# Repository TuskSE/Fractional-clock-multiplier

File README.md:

# Fractional Clock Multiplier (wip)
8hp algorithmic rhythm-generation module for Eurorack, powered by the Teensy LC

Currently two main modes:
* Fractional Multiplication and division of steady or slowly-varying clock inputs.
  * No requirement for clock input to be multiple ppqn, as the clock input is predictive. I'd like to update this so it can deal with swung input also
* Generation of euclidean rhythms ( see [Toussaint 2005](http://cgm.cs.mcgill.ca/~godfried/publications/banff.pdf) ) from arbitrary (regular or non-regular) clock input 

Output can be shifted either by beat-quantized or subquantized amounts, and optionally recombined with the input. This can be used to generate swung clock output for example, or controlled via CV to generate complex compound rhythms. 

Selectable trigger/gate output modes. 

Assignable CV control over all paramaters, with attenuverter. 

Current schematic, panel mockup and PCB design:

An older prototype:

<img src="https://lh3.googleusercontent.com/F2FJkoGD_2Y6mUCA_72Tr9jKIQL8T51u-yPpXMLdA85AF7AUzsiI0R6vGA8PAkv26-s6BQ4YR2C6YWq7D_WIugwAtMuLFM5RAIA3TbphAoilKe7S2X2kTRAt2BslmQAuLZtmlxdI60x7pljAAfFQjpe4ux4xAhEyvlYldTjiMu7CKEfx0s5RLvJsloXXFzuWYh74JVn_ynYBdR5kknDmDOABy-btkMf6ygelY21k-5Sk13OeYi_4nqbalsbw_Kay20YbHjPqkHRQ4EJwRg-HghsKRhGDjyb66y0XgOmLnHMniq8GFPWXzc7Ou17aOJmmEo-iptwhYquIdqMTw5126-4uQ4JN-fbZk5uMNa9TVr03RODQvABWOTEXRQ_gDacrYwKTu132whdYeGTQyy62glm7S0VYDMBLstyA9ZoxIxASJSf1TfdZvlR_91Kjug58e2I4FfsrTAtsJv_XrMFEXS_7mEBVeCH8DtkX2JoZfap947LTTdUUM3774dLUCF0JQwhfHeQYcQB1SFDA_VuOWtunsMsptIcdduzY5Tzj0rUNz_ZlazPewN_-AXO6eQbNcRoDB-4Ui7olnvTiXXzi2Du11re9mQ5SKkCuvxOnhPKEgmTtcn4kvNJcX3Qh0wEJHBKgqk0u13XQsy_8YfT3gf7GZKwuK8Y=w1330-h998-no" width="400" /> 
<img src="https://lh3.googleusercontent.com/jPlmeRyYHMEHQya63Dx3hL95Jbysh51vPWjdv0qWgl-WZDnvFw_E7UjdrqJFGYYVarH7iVs4ytmAIt0LABBTMHH6kHqQVGqYLSZLEW5gPa8H3oHkbPxZTMx4I1T8MirXX7wVHkFoZWimfaWsqIIgXPTuIJBbMEjeAzE6sdcyDQqNuGQdyXbF5uvd4dFsKb_3YRW6z8pEORVFEjMzekyBIoWQ0fae7UkBQnq0ZUeUsCjOyUTfJT4XScNNX3XcO8POUDrKwBvbkCi99yS22Z2fRHsxLioD7h6N1Tmqi0g-oB0sq_DcU2eDUo2e5Gb--74-7LbpuXSUz5ogKjD6iEGw0YnRVUEzRduWnBp71nQx6NfPfPymkGFj7QnaaJ3NyCzc8BOMhg7e9cG51Zjv-tQhav2DePmTunMwQUr27Ihcj0yp49WF03-9ZvHfPJ3tDSSp0pwqf31c9F4NayC2lvPpkkiMVsOQTXKi6ljk3kYxlaiO2Fg_8TIDArlpTC2xMDEHu4DV2MgCgSRlWVBEi4ztONQhaF4s8LsXI4rtHVcNCxsFCfL-9D9fdosnfCruD826B8dtw0TuZPW_jOtZ0NKaQcxt5UMTQD7lKvYxRfEgLSBl8_rl6_8IortW-olTqhssQ1F4xKqM6MwXBvdBJUlQVd7ExVZlULE=w1330-h998-no" width="400" />

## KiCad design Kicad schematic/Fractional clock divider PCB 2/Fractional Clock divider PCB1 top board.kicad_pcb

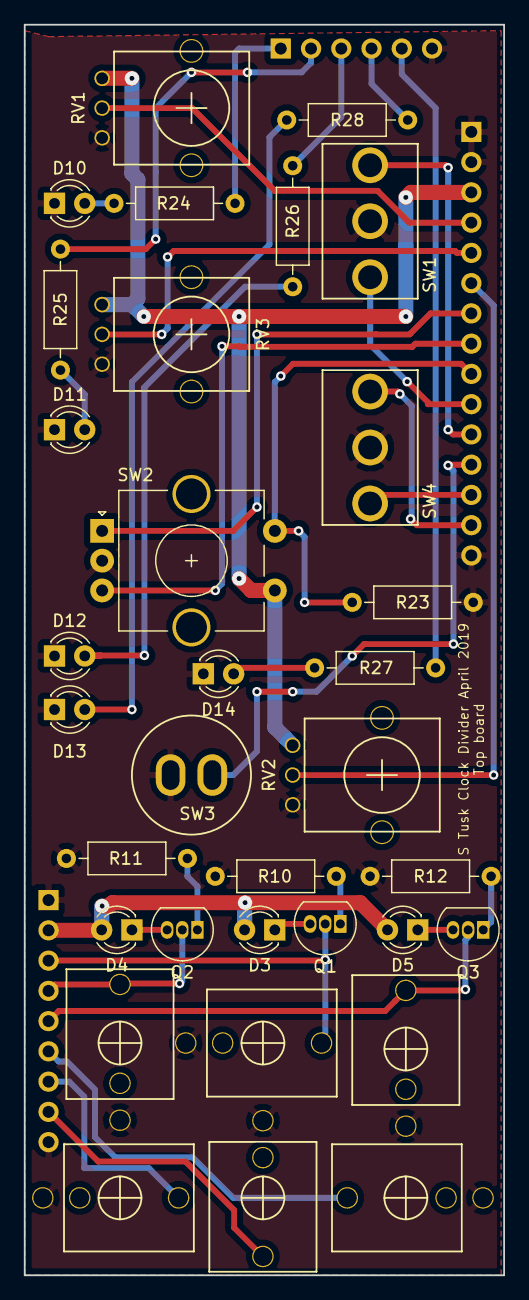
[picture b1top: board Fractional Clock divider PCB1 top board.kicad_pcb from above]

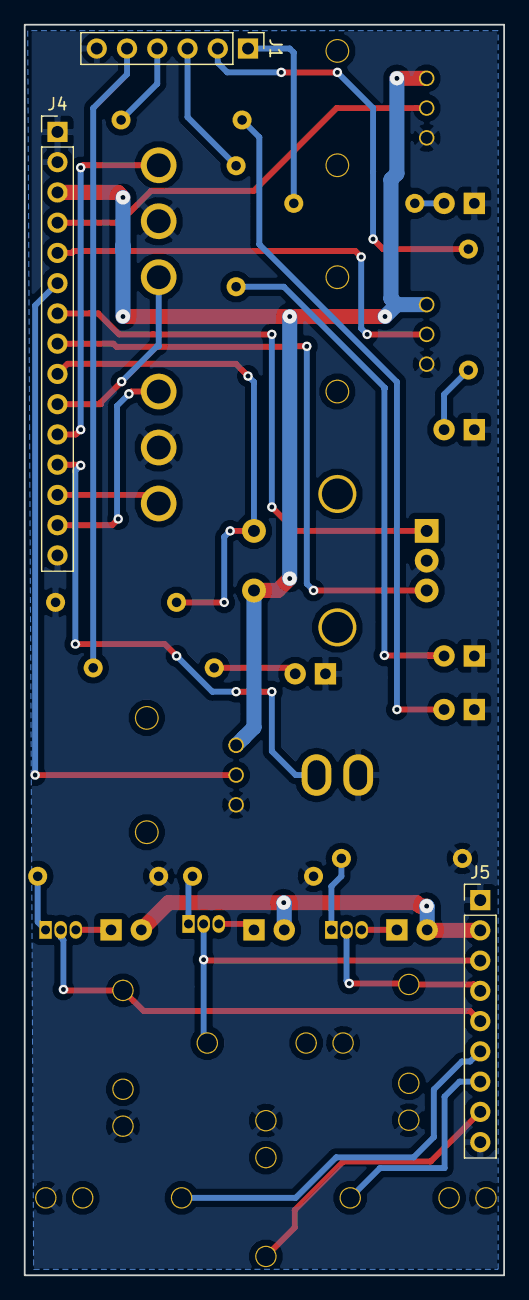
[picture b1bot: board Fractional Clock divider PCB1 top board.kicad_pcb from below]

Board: 2 copper layers, 40.2 x 105.0 mm, 36 parts (3 on the bottom side), 36 nets.

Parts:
CV_in1: PJ301M-12
CycleOutJack1: PJ301M-12
D3, D4, D5, D10, D11, D12, D13, D14: LED; LED_D3.0mm
DigiOutJack1: PJ301M-12
DigiThruJack1: PJ301M-12
J1: Conn_01x06_Female; PinHeader_1x06_P2.54mm_Vertical
J4: Conn_01x15_Female; PinHeader_1x15_P2.54mm_Vertical
J5: Conn_01x09_Female; PinHeader_1x09_P2.54mm_Vertical
Q1, Q2, Q3: 2N3904; TO-92_Inline
R10, R11, R12: 15k; R_Axial_DIN0207_L6.3mm_D2.5mm_P10.16mm_Horizontal
R23: 100k; R_Axial_DIN0207_L6.3mm_D2.5mm_P10.16mm_Horizontal
R24, R25, R26, R28: 1k; R_Axial_DIN0207_L6.3mm_D2.5mm_P10.16mm_Horizontal
R27: 330; R_Axial_DIN0207_L6.3mm_D2.5mm_P10.16mm_Horizontal
RV1, RV2, RV3: 10k; Alpha9mmPot
Reset_In1: PJ301M-12
SW1, SW4: SW_SPDT_MSM; SPDT toggle on-off-on
SW2: Rotary_Encoder_Switch; RotaryEncoder_Alps_EC11E-Switch_Vertical_H20mm_CircularMoun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
SW3: SW_SPST; SPST momentary push PBS105
Trigger/Clock_in1: PJ301M-12

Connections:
+12V: D3.2, D4.2, D5.2, J5.2
/+3_3V: J4.3, RV1.1, RV2.1, RV3.1, SW2.S1
/CLin_F: J5.7, Trigger/Clock_in1.3
/CVin_F: CV_in1.3, J5.6
/EncoderA_F: J4.7, SW2.A
/EncoderB_F: J4.8, SW2.B
/EncoderSw_F: J4.9, R23.1, SW2.S2
/LED_D_F: J1.2, R25.2
/LED_L_F: J1.1, R24.2
/LED_Sh_F: J1.5, R27.2
/Led_ShCV_F: J1.4, R28.2
/Led_Shi_F: J1.3, R26.2
/OutC_F: CycleOutJack1.3, J5.3, Q1.2
/OutM_F: DigiOutJack1.3, J5.4, Q2.2
/OutT_F: DigiThruJack1.3, J5.5, Q3.2
/Pot_CVamt_F: J4.6, RV2.2
/Pot_Divisions_F: J4.5, RV3.2
/Pot_Length_F: J4.4, RV1.2
/Rin_F: J5.8, Reset_In1.3
/SW_CVassgn_F: J4.12, SW3.2
/SW_DivEuc1_F: J4.10, SW1.1
/SW_DivEuc2_F: J4.11, SW1.3
/SW_OutMode1_F: J4.13, SW4.1
/SW_OutMode2_F: J4.14, SW4.3
GND: CV_in1.1, CycleOutJack1.1, D10.1, D11.1, D12.1, D13.1, D14.1, DigiOutJack1.1, DigiThruJack1.1, J1.6, J4.1, J4.2, J4.15, J5.1, J5.9, R10.1, R11.1, R12.1, R23.2, RV1.3, RV2.3, RV3.3, Reset_In1.1, SW1.2, SW2.C, SW3.1, SW4.2, Trigger/Clock_in1.1
unnamed: D3.1, Q1.3
unnamed: D4.1, Q2.3
unnamed: D5.1, Q3.3
unnamed: D10.2, R24.1
unnamed: D11.2, R25.1
unnamed: D12.2, R26.1
unnamed: D13.2, R28.1
unnamed: D14.2, R27.1
unnamed: Q1.1, R10.2
unnamed: Q2.1, R11.2
unnamed: Q3.1, R12.2

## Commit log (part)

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2018-10-12 Update Software/Main/Main.ino
    Impletemented a basic tap tempo on a breadboard.
2018-10-13 Update Software/Main/Main.ino
    Added miltiple outputs, wired up to LEDs on a breadboard.
    With fractional time intervals, LEDs quickly lose synchronization.
2018-10-16 Update Software/Main/Main.ino
    Locked the reset of all clocks to the slowest clock, which seems to work ok, but doesn't really reflect the final configuration we're looking for.
    Aside: i realized that beyond a certian point it's going to be difficult to uncover synchronization problems using only the LEDs. It would be better to use audio signals to hear whether things are re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
    i.e. I think I really need to get hardware prototyped already.
2018-11-01 finizalized schamatic of prototype
2018-11-01 Changed output voltages to 5V.
    Changed all output voltages to 5V.
2018-11-01 Resistor substitution
    Substituting resisitors to reflect what I have at-hand
2018-11-02 Resistor substitution
    Again, substitution to match components I have on-hand
2018-11-02 Resistor substitutions
2018-11-03 Fixed LED output
    Fixed a hardware bug with the output LEDs: the current going into the transitior base was not being limited.
2018-11-12 circuit bugfixes
    Circuit bugfixes:
    Added pulldown resistor to the encoder switch
    Changed feedback resistor on the input CV opamp, to keep it within the correct voltage range. My choice (15k) was probably a little conservative - on testing, the voltage seen by the teensy can't go 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
2018-11-13 Intial testing (and bugfixing) of prototype build
2018-11-20 Added code to read pot values
2018-11-22 Started PulsePredictor class
    Started building a class of objects to relay incoming pulses, and/or form predictions about when future pulses will arrive. untested.
2018-11-23 Pulse thru using PulsePredictor class
    Finished setting up the PulsePredictor class. Managed to get it passing pulses straight through to the output.
    However, I only get proper triggering if I add a >=1ms delay in the loop. I suspect this is because pulses are otherwise too short to trigger my other modules. Next on the to-do list is to make an ob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
2018-11-24 Trigger out manager
    Added a class to handle outputting triggers. i.e. you trigger output, and it makes sure the signal continues to be sent for a specified (hardcoded) time.
2018-11-24 ClockDivider/Multiplier
    Added an object to control clock division/multiplication.
    Currently, there's a bug whereby even multiples (e.g. 4 out over 2 in) work ok, but more complex polyrhythms (e.g. 3 out over 2 in) dont give the correct output
2018-11-24 Bug fixed
    Simple bug- fixed.
    Now working as intended, but without dynamic control of paramaters via knobs/CV. That's next on the to do list...
2018-11-27 Started code to handle divider/multiplier CV/knob changes mid-cycle
2018-12-02 Length pot control, jitter smoother
    Wired up the length pot to control changes in cycle lengh.
    There werre problems with jitter in the knob voltage - I've tried a simpe fix, but it's bugged. I think because if it throws away a new datapoint on the nth iteration, the next iteration is looking b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
2018-12-03 Fixed anti-jitter code
2018-12-03 Reading multiple pots - problematic!
    Upon testing, realized that it's nontrivial to read multiple analog inputs at the kind of speeds i would like. At the moment, if I read fast, there is crosstalk between the channels, presumably becau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
    Need to dig in the code of ornament & crime etc to see how they get around this. Alternative is to change the hardware. (External ADC?)
2018-12-08 Changes of Length and Divison knobs now work as expected
2018-12-28 Encoder
    Got readings from encoder, after a little troubleshooting. Next job: actually wire it up to shift/shuffle
2018-12-29 Shift control -Div/Mult mode
    In Div/Mult mode, the encoder now shifts (by integer amounts) our position in the input cycle. (as one might use, for example, to synchronise the cycle starts on input and output clocks.)
2018-12-29 Shuffle Control - Div/Mult mode
    In Div/Mult mode, turning the encoder with the encoder switch pushed down now delays output pulses by 0 to 1 beats.
    Brightness of the shuffle led indicates the extent of shuffle, but the brightness response doesn't seem very linear to me, so it's not exceptionally useful.
    To do: implement CV control over enocder functions.
2018-12-30 CV control
    Made a start on CV control. Reading CV switch assignment.
    To do:
    - Figure out how to calibrate the CV input to recognise 0v in, and scale accoridngly
    - figure out how to route the CV input into the appropriate control signal.
2018-12-30 CV control
    Fleshed out the functions which read the control voltage, and attenuvert it based on the setting of the attenuverter knob.
    There are some (hardware?) issues - e.g then the jack isn't plugged, there's quite a lot of noise on the input.
    I've tidied up the way that the (length and divisions) knobs are read, to make it simpler to add the attenuated control voltage value to the knob reading directly, before scaling to the desired param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
    Haven't started implemetation of CV control over the encoder functions (shift/shuffle).
2018-12-31 CV control
    CV control over length/division implemented fully.
    Made a start on control over Shift. CVassigner::ReturnShiftModifier() needs testing, and plugging into the shift function.
2019-01-04 CV control over shift
    I think CV control over shift works now, but I've somehow broken the division/multiplication code. The jitter smoother doesn't seem to perform properly any more (massive lag), and the divider output 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
2019-01-04 Revert "CV control over shift"
    This reverts commit d19ce64adabfa426d813e32895e127e230ccecf6.
2019-01-04 Revert "CV control"
    This reverts commit 9678daa802b3669ac48b2bf6e4cd711890e735c7.
2019-01-04 Restore Dec31st commit
    REstored the Dec 31st commit line-by line, with a few ommisions, tidying a few things up on the way.
    At first, div/mult code worked ok but not CV control. In trying to fix that, I think I re-introduced the issue: it definitely seems to be related to the jitter smoother.
    Jitter smoother seems to be reading the wrong input - not picking up the signal from the knob.
    Removed the jitter smoothing for now.
2019-01-05 CV control over shift and shuffle
    CV control implemented over shift / shuffle.
    A few caveats:
    - We don't have enough switch positions currently to allow both shift and shuffle as options. I hope to fix that in the next hardware iteration...
    - The effect of noise in the CV input in causing big problems (constant skipping between paramater values.) I think we probably need more sophisticated smoothing
2019-01-06 CV jitter fix
    Smoothed out noise/jitter in CV control over Shift/Shuffle functions, which actually came from reading the attenuverter/knob voltage without smoothing.
2019-02-25 Barebones euclidean rhythm generator
    Basic generation seems to work ok.
    To do next:
    Live update of paramater values -> is the compuitation time tolerably small?
    Allow shuffling of the polygon
    Explore quantization to the nearest quantization point in either direction round the circle. Can it generate the son clave?
2019-03-14 Identified bug in CV control over shuffle, started plumbing euclidean generator into main()
    Implemented basic knob control for the euclidean pattern generator
    started putting calls to the euclidean pattern generator in the main code cycle
    however, found a bug in CV control over fractional shuffle: When we increase the CV/shuffle amount in between the [time the pulse would be at with 0 shuffle] and [time the pulse should be at with the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
2019-03-15 bug hunting
    I've still failed to find the source of the bug: output pulses (clock divider mode) stop while the CV attenuverter or CV in signal is rapidly altered.
    I think the right PositionInOutputCycle is set by DividerMultiplier::CalculateOutputTimesMidCycle, but when I look in DividerMultiplier::ShouldWeOutputMainPulse, it often seems wrong.
    One thing to consider: is it faulty that we only loop the Output cycle back to the beginning when the Input cycle resets?
2019-03-22 Bug fix
    Fixed the bug where output beats could be missed immediately after the shuffle CV was altered. Did some tidying up along the way.
    There's at least one remaining bug: after a certain point we stop getting (divider/multiplier) output pulses, even though the PositionInOutputCycle value keeps cycling as expected
2019-03-22 Fixed micros() rollover bug
    Implemented a more sensible way of handing micros() rollover.
    However, I haven't testeed up until the rollover point. I just know that a previous bug where output stopped after a a few minutes no longer occurs.
    I also changed the polarity of CV effect on fractional shuffle - it's more intuitive this way.
2019-03-23 Euclidean Rhythm generation
    Finished the euclidean rhythm generation code, and plugged it into the main loop - it now works as expected, with knob and cv control.
    To do
    - test CV control over shift works
    - Write something to handle changes between Euclidean and Mult/Div modes
    - Write something to force cycle resets (in anticiaption of the next hardware revision, which I think should have a cycle reset in)
    - Think about what we can do when hits>quantization
2019-03-25 gate mode + various other
    Checked that CV control over shfit works ok.
    Implemented seamless switching between modes (euclidean / division) from the front panel
    Implemented switchable (from the front panel) gate out mode, in which the Main out outputs gates rather than triggers
2019-03-25 Euclidean mode - snap to closest point
    Added a "snap to closest point" feature in the euclidean mode. Not clear yet whether it really adds anything musically over the regular euclidean mode...
2019-04-12 PCB design
    Finalized PCB design.
2019-04-12 PCB renders, panel mockup
2019-04-26 Code update to reflect PCB design
    Updating code to reflect
    -changes in pins
    -new CV assignment method
    -new mode slect configuration
    Seems to work, but having assembled the first version of the PCB there's quite a few errors to fix before we take development any further...
2019-04-27 PCB rework
    Reworked PCB design to
    -Add PCB panel
    -correct knob orientation
    -rearrange panel to make more space for labels
    -easier-to-solder footprints for jacks and transistors
    -correct silkscreen-label switcheroos
2019-05-23 Code update to reflect second PCB design
    - Updated CV destination selection code to match new PCB+panel design
    - Found that potentiometer backlash and non-linearity precented knob pointers from matching panel ticks. To solve this, I implemented a very janky calibration procedure, which prints output over seri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
    - Updated code to allow "divisions" = 0 ( => no output, in either mode. )
    - reduced severity of anti-jitter correction on the knobs - readings are much less noisy now that 100k pots have been replaced with 10k
    To do:
    - try and increase the brightness of
2019-05-23 Added functionality to reset input
    Added code to make use of the reset input
2019-05-25 Bug fixes in shuffle and CV handling
    -changed the guts of the shuffle handling to make led brightness better behaved at shuffle = 1. (Still to do: lookup tables for more linear LED brightness)
    -reduced smoothing on the CV input.
2019-05-25 Shuffle LED linearity
    Impletemented more linear scaling of the shuffle LED, using a LUT
2019-05-25 Made a start on allowing euclidean and divider modes to run simultaneously
